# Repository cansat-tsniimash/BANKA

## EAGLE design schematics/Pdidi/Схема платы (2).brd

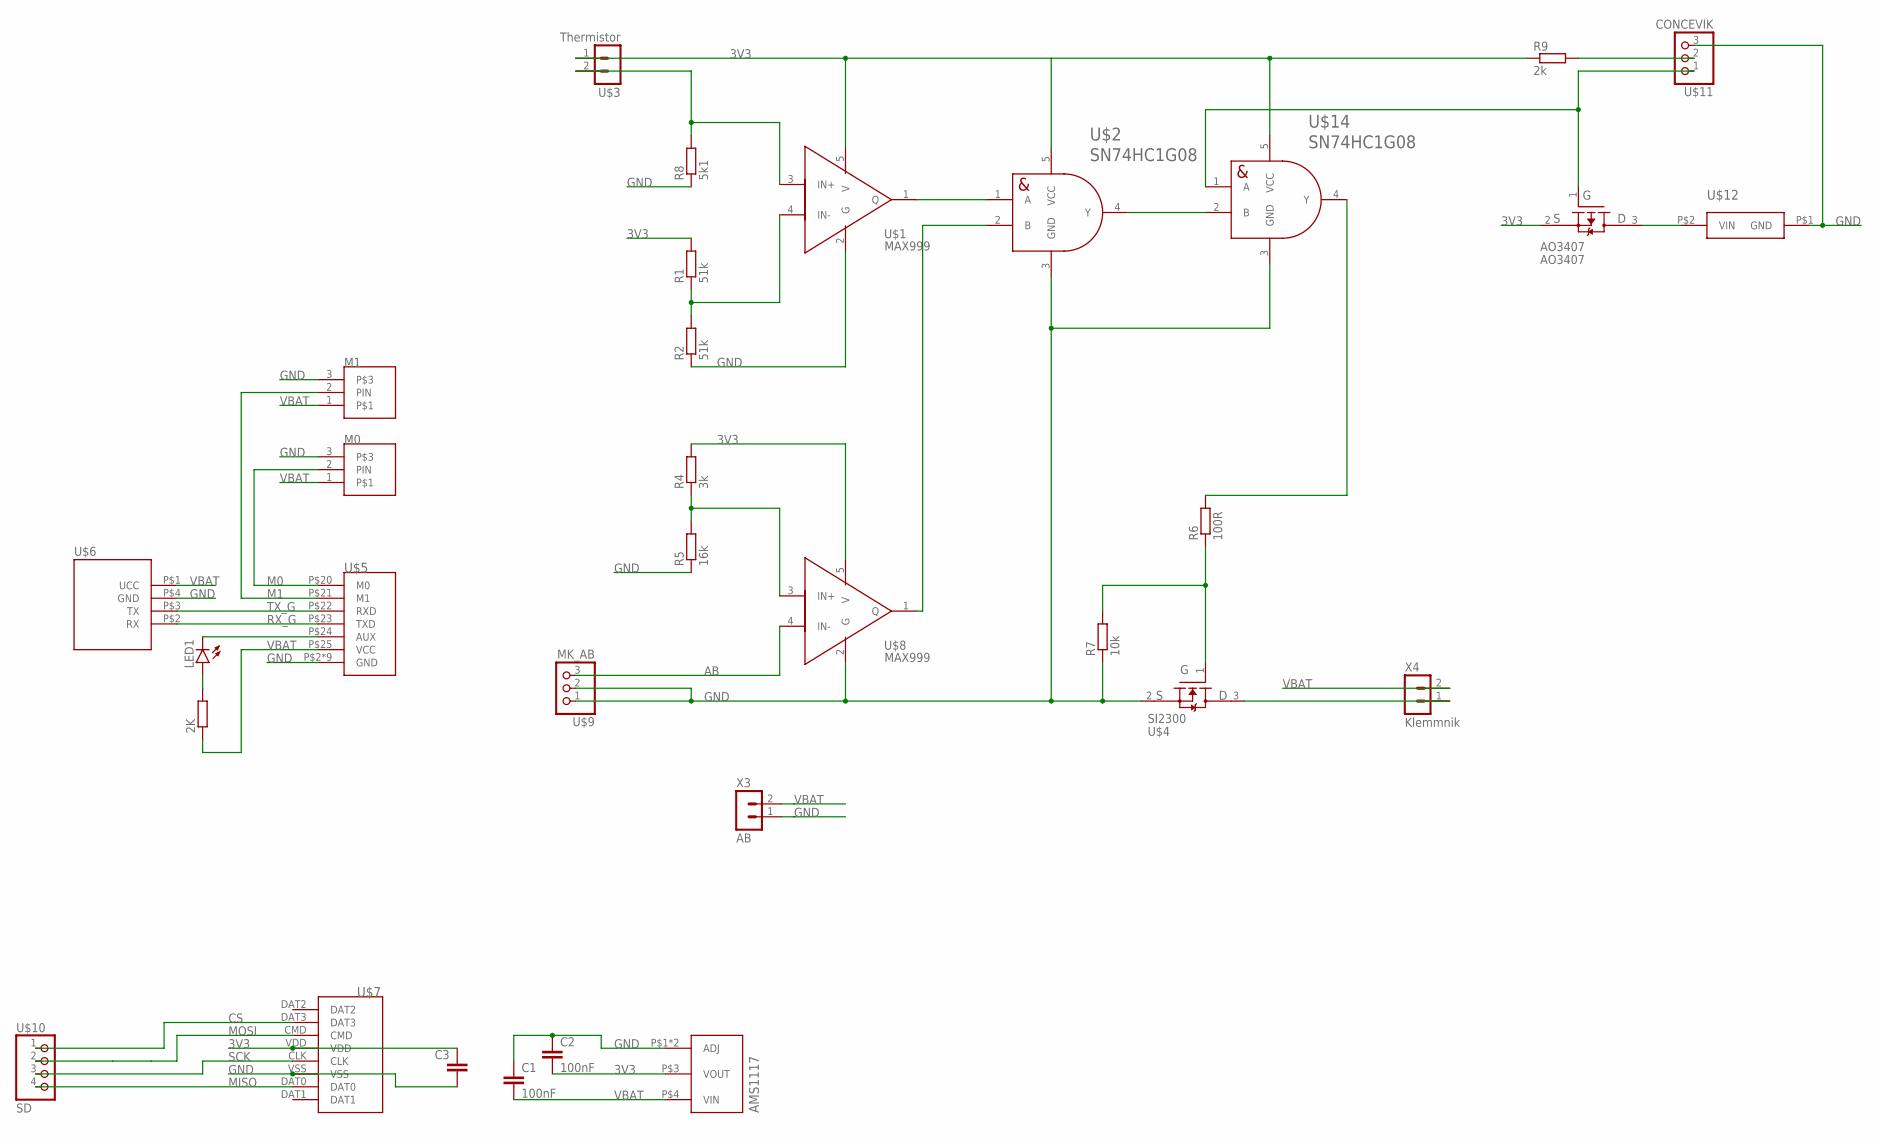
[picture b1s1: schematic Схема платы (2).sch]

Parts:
2K: R-EU_R0603; R0603
AMS1117: AMS1117; SOT223
AO3407: AO3407; SOT23-3
C1, C2: 100nF; C0603
C3: C-EUC0603; C0603
LED1: LEDCHIP-LED0603; CHIP-LED0603
M0, M1: CONNECT_3
R1, R2: 51k; R0603
R4: 3k; R0603
R5: 16k; R0603
R6: 100R; R0603
R7: 10k; R0603
R8: 5k1; R0603
R9: 2k; R0603
U$1, U$8: MAX999; SOT23-5
U$2, U$14: SN74HC1G08; SOT23-5
U$3: Thermistor; 53047-02
U$4: SI2300; SOT23-3
U$5: E220-400T22S
U$6: GPS-NEO7M
U$7: SD
U$9: MK_AB; 53047-03
U$10: SD; 53047-04
U$11: CONCEVIK; 53047-03
U$12: BUZZERS8R6; BUZZER-S8R12
X3: AB; JST-2-2.5
X4: Klemmnik; JST-2-2.5

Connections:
3V3: AMS1117.P$3 (VOUT), AO3407.2 (PS), C2.2, C3.1, R1.2, R4.2, R9.2, U$1.5 (V), U$2.5 (VCC), U$3.1, U$7.VDD, U$8.5 (V), U$14.5 (VCC)
AB: U$8.4 (IN-), U$9.3
CS: U$7.DAT3, U$10.1
GND: AMS1117.P$1 (ADJ), AMS1117.P$2 (ADJ), C1.1, C2.1, C3.2, M0.3, M1.3, R2.1, R5.1, R7.1, R8.1, U$1.2 (G), U$2.3 (GND), U$4.2 (NS), U$5.P$2 (GND), U$5.P$8 (GND), U$5.P$11 (GND), U$5.P$13 (GND), U$5.P$14 (GND), U$5.P$15 (GND), U$5.P$16 (GND), U$5.P$19 (GND), U$5.P$26 (GND), U$6.P$4 (GND), U$7.VSS, U$8.2 (G), U$9.1, U$9.2, U$11.3, U$12.P$1 (GND), U$14.3 (GND), X3.1
M0: M0.2 (PIN), U$5.P$20 (M0)
M1: M1.2 (PIN), U$5.P$21 (M1)
MISO: U$7.DAT0, U$10.4
MOSI: U$7.CMD, U$10.2
unnamed: R8.2, U$1.3 (IN+), U$3.2
unnamed: R9.1, U$11.2
unnamed: R4.1, R5.2, U$8.3 (IN+)
unnamed: 2K.2, LED1.A
unnamed: LED1.C, U$5.P$24 (AUX)
unnamed: R1.1, R2.2, U$1.4 (IN-)
unnamed: U$1.1 (Q), U$2.1 (A)
unnamed: U$2.2 (B), U$8.1 (Q)
unnamed: U$4.3 (ND), X4.1
unnamed: U$2.4 (Y), U$14.2 (B)
unnamed: R6.1, R7.2, U$4.1 (NG)
unnamed: AO3407.3 (PD), U$12.P$2 (VIN)
unnamed: AO3407.1 (PG), U$11.1, U$14.1 (A)
unnamed: R6.2, U$14.4 (Y)
RX_G: U$5.P$23 (TXD), U$6.P$2 (RX)
SCK: U$7.CLK, U$10.3
TX_G: U$5.P$22 (RXD), U$6.P$3 (TX)
VBAT: 2K.1, AMS1117.P$4 (VIN), C1.2, M0.1, M1.1, U$5.P$25 (VCC), U$6.P$1 (UCC), X3.2, X4.2

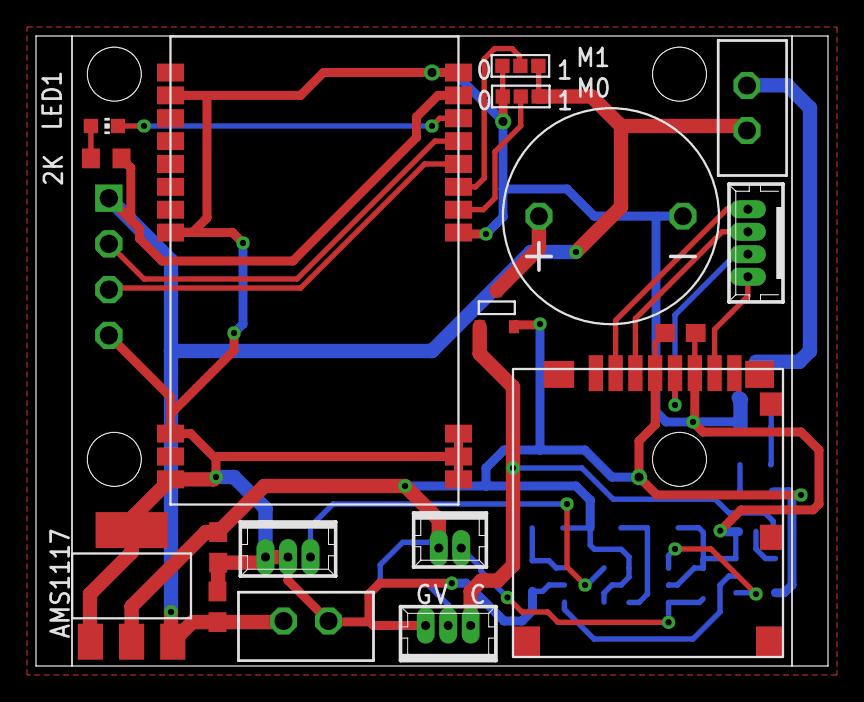
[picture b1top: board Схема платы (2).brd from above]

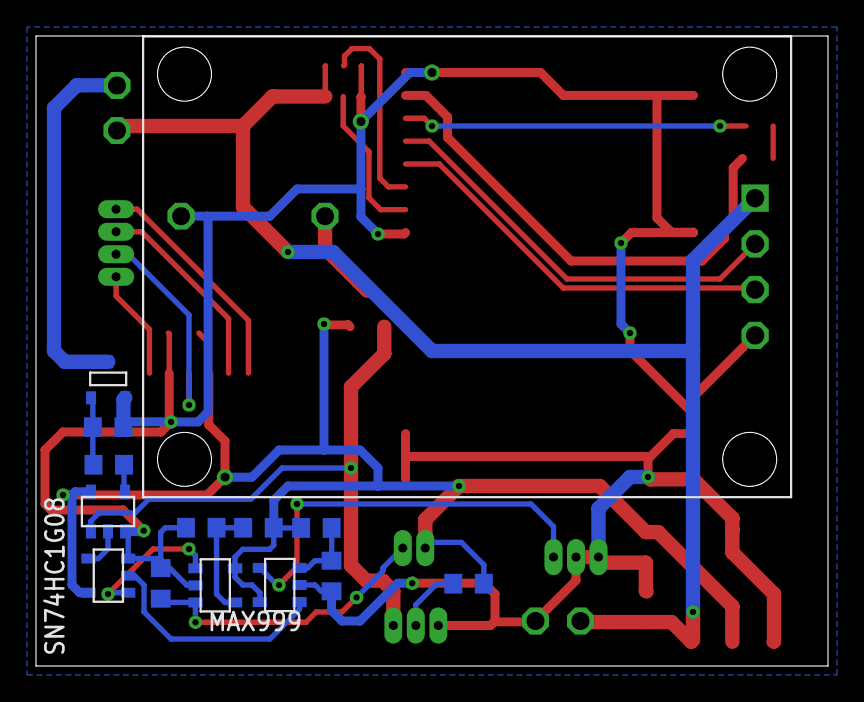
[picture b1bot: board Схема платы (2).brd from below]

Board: 2 copper layers, 44.0 x 35.0 mm, 32 parts (14 on the bottom side), 26 nets.

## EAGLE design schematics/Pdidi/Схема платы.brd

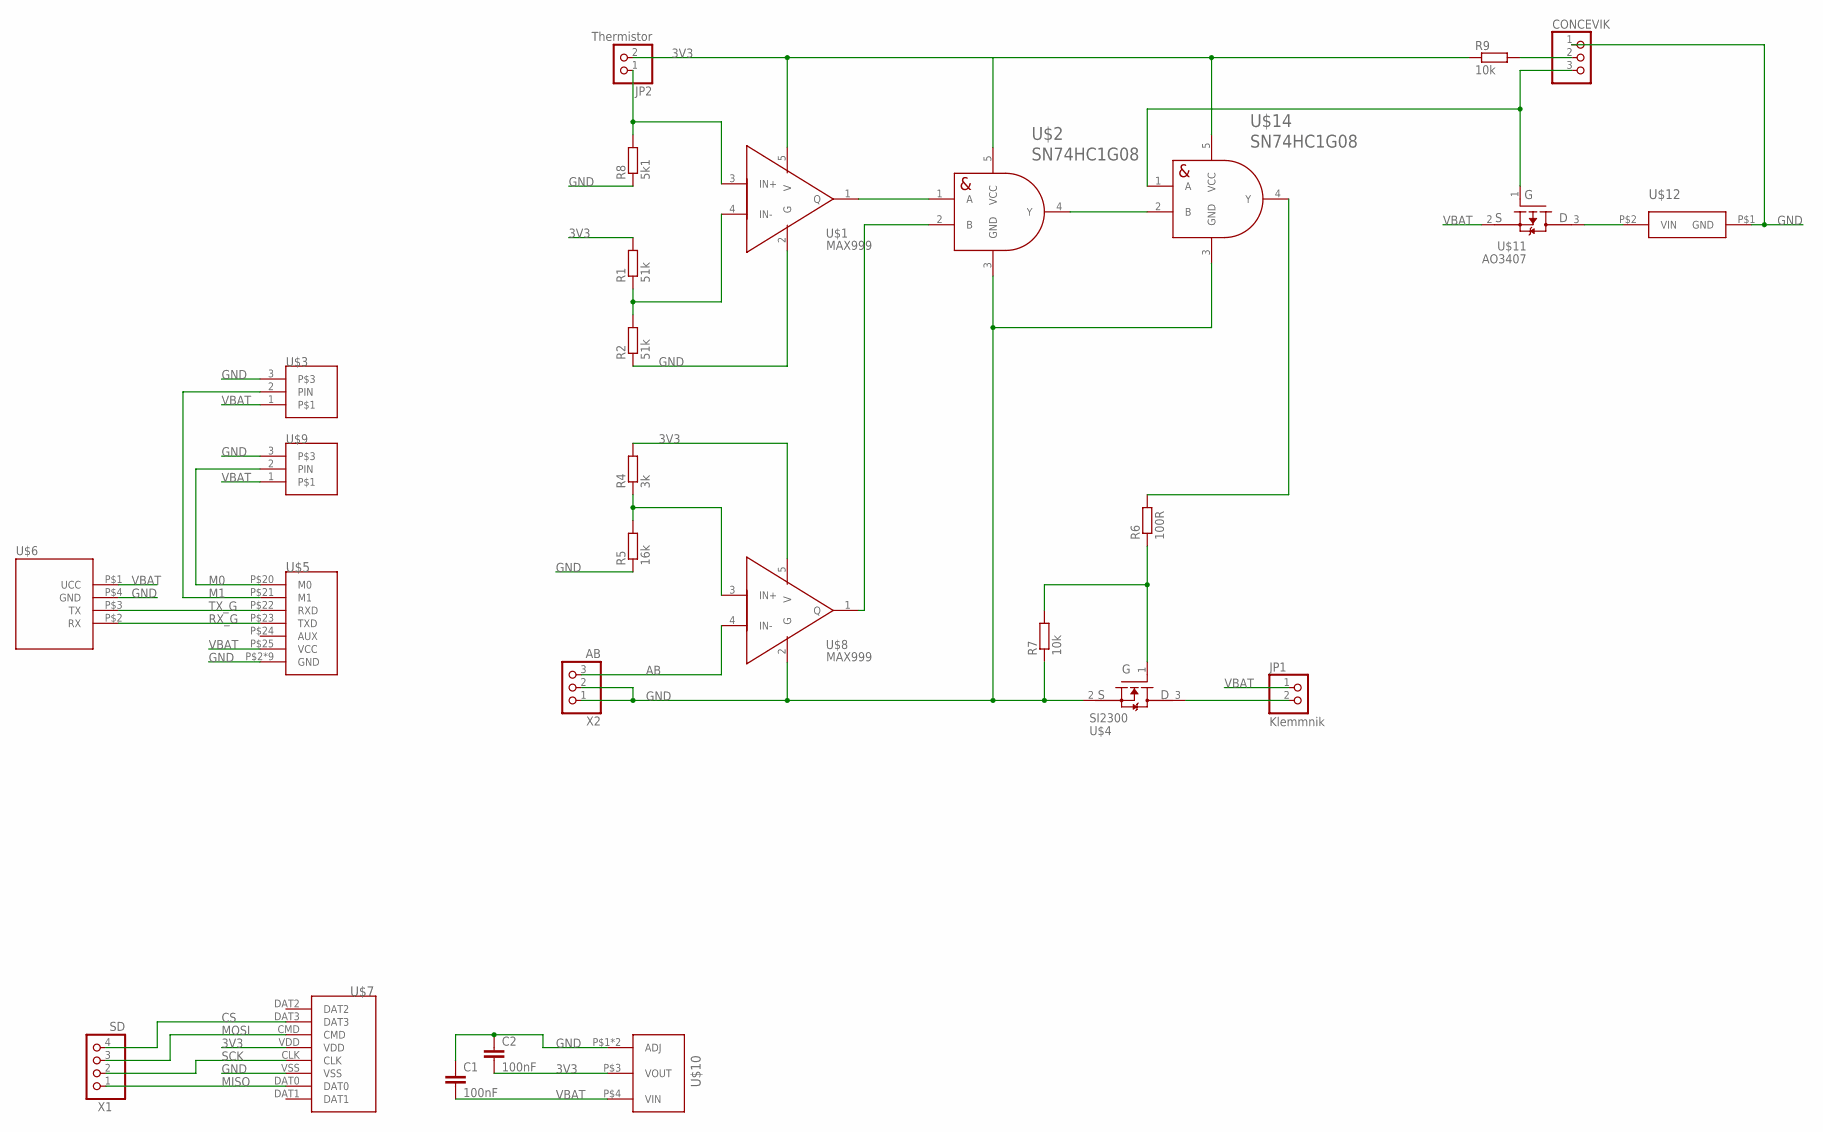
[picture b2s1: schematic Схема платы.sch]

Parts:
C1, C2: 100nF; C0603
CONCEVIK: PINHD-1X3; 1X03
JP1: Klemmnik; 1X02
JP2: Thermistor; 1X02
R1, R2: 51k; R0603
R4: 3k; R0603
R5: 16k; R0603
R6: 100R; R0603
R7, R9: 10k; R0603
R8: 5k1; R0603
U$1, U$8: MAX999; SOT23-5
U$2, U$14: SN74HC1G08; SOT23-5
U$3, U$9: CONNECT_3
U$4: SI2300; SOT23-3
U$5: E220-400T22S
U$6: GPS-NEO7M
U$7: SD
U$10: AMS1117; SOT223
U$11: AO3407; SOT23-3
U$12: BUZZERS8R6; BUZZER-S8R12
X1: SD; 1X04
X2: AB; 1X03

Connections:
3V3: C2.2, JP2.2, R1.2, R4.2, R9.2, U$1.5 (V), U$2.5 (VCC), U$7.VDD, U$8.5 (V), U$10.P$3 (VOUT), U$14.5 (VCC)
AB: U$8.4 (IN-), X2.3
CS: U$7.DAT3, X1.4
GND: C1.1, C2.1, CONCEVIK.1, R2.1, R5.1, R7.1, R8.1, U$1.2 (G), U$2.3 (GND), U$3.3, U$4.2 (NS), U$5.P$2 (GND), U$5.P$8 (GND), U$5.P$11 (GND), U$5.P$13 (GND), U$5.P$14 (GND), U$5.P$15 (GND), U$5.P$16 (GND), U$5.P$19 (GND), U$5.P$26 (GND), U$6.P$4 (GND), U$7.VSS, U$8.2 (G), U$9.3, U$10.P$1 (ADJ), U$10.P$2 (ADJ), U$12.P$1 (GND), U$14.3 (GND), X2.1, X2.2
M0: U$5.P$20 (M0), U$9.2 (PIN)
M1: U$3.2 (PIN), U$5.P$21 (M1)
MISO: U$7.DAT0, X1.1
MOSI: U$7.CMD, X1.3
unnamed: JP2.1, R8.2, U$1.3 (IN+)
unnamed: CONCEVIK.2, R9.1
unnamed: R4.1, R5.2, U$8.3 (IN+)
unnamed: R1.1, R2.2, U$1.4 (IN-)
unnamed: U$1.1 (Q), U$2.1 (A)
unnamed: U$2.2 (B), U$8.1 (Q)
unnamed: JP1.2, U$4.3 (ND)
unnamed: U$2.4 (Y), U$14.2 (B)
unnamed: R6.1, R7.2, U$4.1 (NG)
unnamed: U$11.3 (PD), U$12.P$2 (VIN)
unnamed: CONCEVIK.3, U$11.1 (PG), U$14.1 (A)
unnamed: R6.2, U$14.4 (Y)
RX_G: U$5.P$23 (TXD), U$6.P$2 (RX)
SCK: U$7.CLK, X1.2
TX_G: U$5.P$22 (RXD), U$6.P$3 (TX)
VBAT: C1.2, JP1.1, U$3.1, U$5.P$25 (VCC), U$6.P$1 (UCC), U$9.1, U$10.P$4 (VIN), U$11.2 (PS)

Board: 2 copper layers, 28 parts (1 on the bottom side), 24 nets, no tracks yet.

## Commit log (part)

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2025-12-09 initial
2026-02-11 added code project
2026-02-11 Добавил схемы прост как они есть сейчас, чтобы не потерять
2026-02-11 продлжаем писать драйвер, добавили лампочку
2026-02-14 написали дрова для ds18b20
2026-03-28 загрузил модели крео
2026-03-28 небольшие правки для упрощения печати
2026-03-28 bmp280_v1
2026-03-28 добавлены функции для проверки
2026-03-28 дописал БМПшку
2026-03-28 Написал GPS
2026-03-28 продолжаю изменять размеры для печати
2026-03-28 написал LSM6DS3
2026-03-28 Начало наземки
2026-03-28 исправил размер конструктора в CREO
2026-03-28 написал lis2mdl
2026-03-28 написал SD
2026-03-28 начал писать SD, исправил lis
2026-03-28 дописал lora
2026-03-28 пишу lora
2026-03-28 Функция парса
2026-04-01 починили лору
2026-04-04 добавили вторую сд, пишем состояния
2026-04-04 написали ADC, написали пищалку
2026-04-11 Починили радио
2026-04-11 Сделал наземку для обязательных 27 байт
2026-04-11 Обязательная часть наземки 27 байт
2026-04-11 Перенесла костыль, показала что надо написать в бмп, расписала комментарии
2026-04-11 Добавила гитигнор
2026-04-11 Поправила датчики
2026-04-14 починили сд
2026-04-25 исправил некоторые todo, пишу состояния
2026-05-17 готовый и рабочий алгоритм, предфинальная версия кода
2026-06-12 начало термистора основного
2026-06-12 продолжение термистора, изменение состояний
2026-06-19 исправление состояний и пакета
